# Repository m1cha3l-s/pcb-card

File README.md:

# m1cha3l's PCB Business card V1
You were luck enough to recieve my pcb business card! You can keep it in your wallet and use the built in ruler or solder the needed components and get a nice desk accessories which has a 6x6 NeoPixel MATRIX, 2 buttons, vibration motor for notifications and a BME280 sensor for presure, humidity and temerature and supports Zigbee, Matter, Thread and bluetooth and wifi.

## Building
You can buy the components I have in my bom to build this together! Also I included headers which you can solder to add more sensors for smart home!

## Firmware
I have included a simple firmware which shows red when the temp from BME280 is over 20℃ and green when under when you press button number 2 and vibrates and shows blue when you press button number 1.
1. Open Arduino IDE
2. Choose seeed xiao ESP32-C6
3. Flash and enjoy!!

## Looks

## Schematic and PCB

## [BOM](https://github.com/m1cha3l-s/pcb-card/blob/main/BOM.csv)

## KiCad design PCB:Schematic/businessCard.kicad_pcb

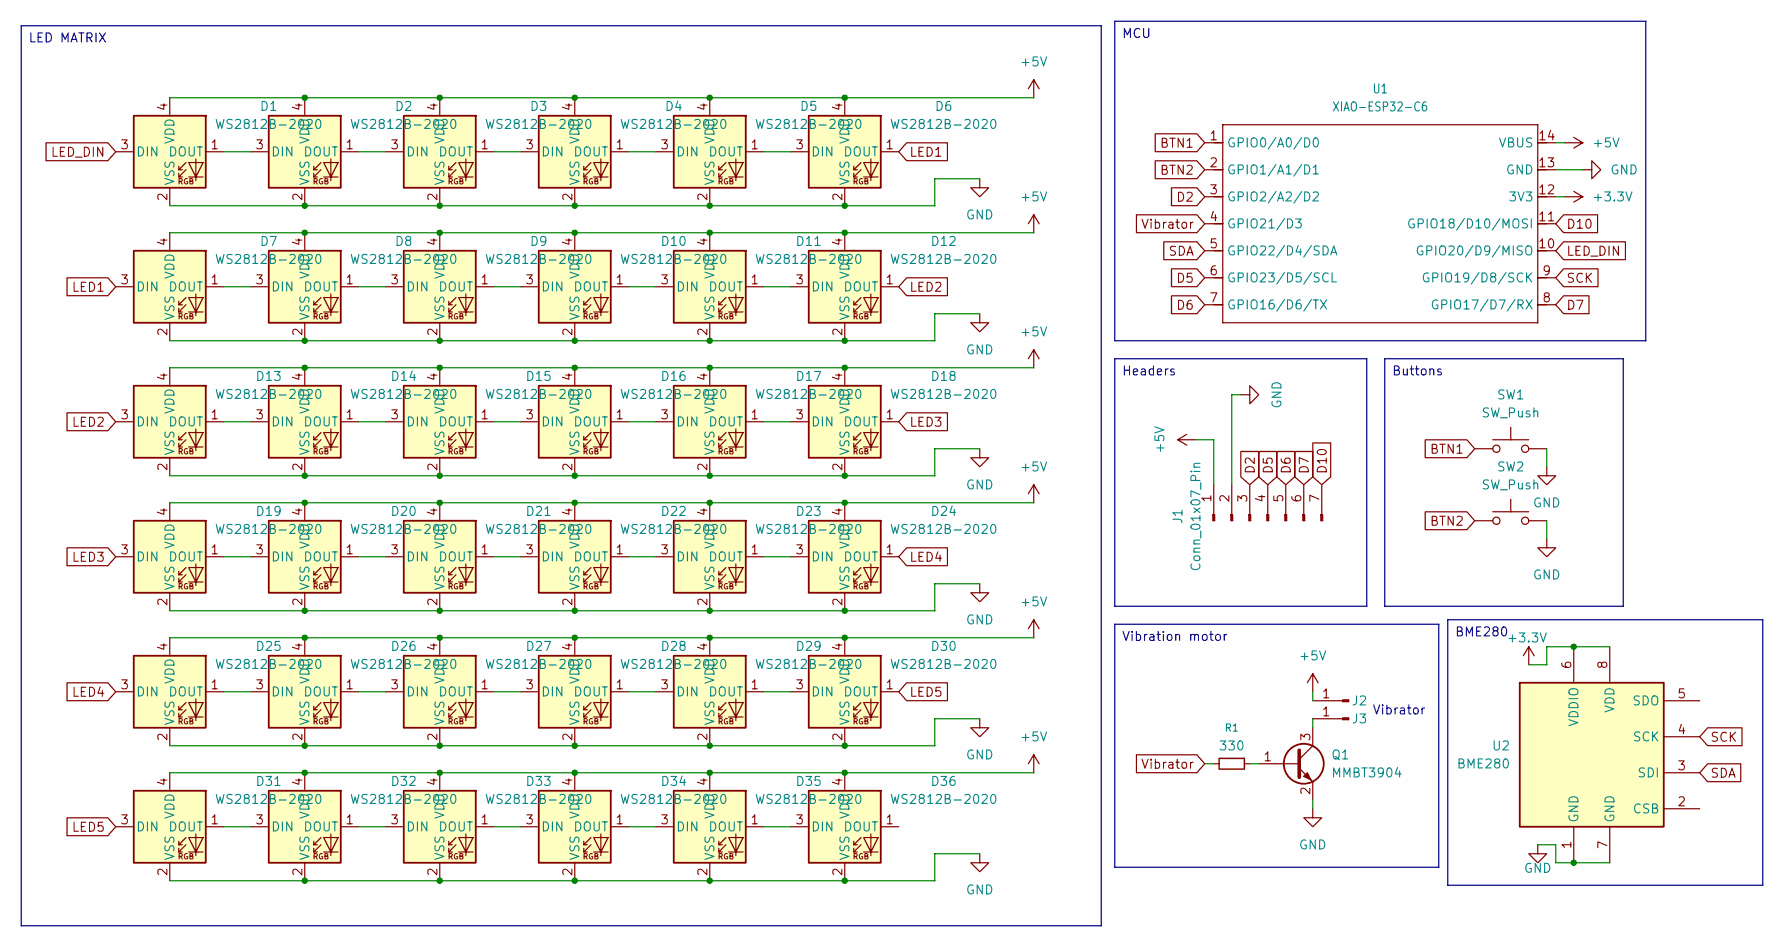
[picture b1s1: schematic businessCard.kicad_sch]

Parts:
D1, D2, D3, D4, D5, D6, D7, D8, D9, D10, D11, D12, D13, D14, D15, D16, D17, D18, D19, D20, D21, D22, D23, D24, D25, D26, D27, D28, D29, D30, D31, D32, D33, D34, D35, D36: WS2812B-2020; LED_WS2812B-2020_PLCC4_2.0x2.0mm
J1: Conn_01x07_Pin; PinHeader_1x07_P2.54mm_Vertical
J2, J3: Conn_01x01_Pin; TestPoint_Pad_2.0x2.0mm
Q1: MMBT3904; SOT-23
R1: 330; R_0603_1608Metric
SW1, SW2: SW_Push; SW_PUSH_6mm_H4.3mm
U1: XIAO-ESP32-C6; XIAO-ESP32C6-DIP
U2: BME280; Bosch_LGA-8_2.5x2.5mm_P0.65mm_ClockwisePinNumbering

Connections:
+3.3V: U1.12 (3V3), U2.6 (VDDIO), U2.8 (VDD)
+5V: D1.4 (VDD), D2.4 (VDD), D3.4 (VDD), D4.4 (VDD), D5.4 (VDD), D6.4 (VDD), D7.4 (VDD), D8.4 (VDD), D9.4 (VDD), D10.4 (VDD), D11.4 (VDD), D12.4 (VDD), D13.4 (VDD), D14.4 (VDD), D15.4 (VDD), D16.4 (VDD), D17.4 (VDD), D18.4 (VDD), D19.4 (VDD), D20.4 (VDD), D21.4 (VDD), D22.4 (VDD), D23.4 (VDD), D24.4 (VDD), D25.4 (VDD), D26.4 (VDD), D27.4 (VDD), D28.4 (VDD), D29.4 (VDD), D30.4 (VDD), D31.4 (VDD), D32.4 (VDD), D33.4 (VDD), D34.4 (VDD), D35.4 (VDD), D36.4 (VDD), J1.1, J2.1, U1.14 (VBUS)
BTN1: SW1.1, U1.1 (GPIO0/A0/D0)
BTN2: SW2.1, U1.2 (GPIO1/A1/D1)
D2: J1.3, U1.3 (GPIO2/A2/D2)
D5: J1.4, U1.6 (GPIO23/D5/SCL)
D6: J1.5, U1.7 (GPIO16/D6/TX)
D7: J1.6, U1.8 (GPIO17/D7/RX)
D10: J1.7, U1.11 (GPIO18/D10/MOSI)
GND: D1.2 (VSS), D2.2 (VSS), D3.2 (VSS), D4.2 (VSS), D5.2 (VSS), D6.2 (VSS), D7.2 (VSS), D8.2 (VSS), D9.2 (VSS), D10.2 (VSS), D11.2 (VSS), D12.2 (VSS), D13.2 (VSS), D14.2 (VSS), D15.2 (VSS), D16.2 (VSS), D17.2 (VSS), D18.2 (VSS), D19.2 (VSS), D20.2 (VSS), D21.2 (VSS), D22.2 (VSS), D23.2 (VSS), D24.2 (VSS), D25.2 (VSS), D26.2 (VSS), D27.2 (VSS), D28.2 (VSS), D29.2 (VSS), D30.2 (VSS), D31.2 (VSS), D32.2 (VSS), D33.2 (VSS), D34.2 (VSS), D35.2 (VSS), D36.2 (VSS), J1.2, Q1.2 (E), SW1.2, SW2.2, U1.13 (GND), U2.1 (GND), U2.7 (GND)
LED1: D6.1 (DOUT), D7.3 (DIN)
LED2: D12.1 (DOUT), D13.3 (DIN)
LED3: D18.1 (DOUT), D19.3 (DIN)
LED4: D24.1 (DOUT), D25.3 (DIN)
LED5: D30.1 (DOUT), D31.3 (DIN)
LED_DIN: D1.3 (DIN), U1.10 (GPIO20/D9/MISO)
unnamed: D1.1 (DOUT), D2.3 (DIN)
unnamed: D2.1 (DOUT), D3.3 (DIN)
unnamed: D3.1 (DOUT), D4.3 (DIN)
unnamed: D4.1 (DOUT), D5.3 (DIN)
unnamed: D5.1 (DOUT), D6.3 (DIN)
unnamed: D7.1 (DOUT), D8.3 (DIN)
unnamed: D8.1 (DOUT), D9.3 (DIN)
unnamed: D9.1 (DOUT), D10.3 (DIN)
unnamed: D10.1 (DOUT), D11.3 (DIN)
unnamed: D11.1 (DOUT), D12.3 (DIN)
unnamed: D13.1 (DOUT), D14.3 (DIN)
unnamed: D14.1 (DOUT), D15.3 (DIN)
unnamed: D15.1 (DOUT), D16.3 (DIN)
unnamed: D16.1 (DOUT), D17.3 (DIN)
unnamed: D17.1 (DOUT), D18.3 (DIN)
unnamed: D19.1 (DOUT), D20.3 (DIN)
unnamed: D20.1 (DOUT), D21.3 (DIN)
unnamed: D21.1 (DOUT), D22.3 (DIN)
unnamed: D22.1 (DOUT), D23.3 (DIN)
unnamed: D23.1 (DOUT), D24.3 (DIN)
unnamed: D25.1 (DOUT), D26.3 (DIN)
unnamed: D26.1 (DOUT), D27.3 (DIN)
unnamed: D27.1 (DOUT), D28.3 (DIN)
unnamed: D28.1 (DOUT), D29.3 (DIN)
unnamed: D29.1 (DOUT), D30.3 (DIN)
unnamed: D31.1 (DOUT), D32.3 (DIN)
unnamed: D32.1 (DOUT), D33.3 (DIN)
unnamed: D33.1 (DOUT), D34.3 (DIN)
unnamed: D34.1 (DOUT), D35.3 (DIN)
unnamed: D35.1 (DOUT), D36.3 (DIN)
unnamed: J3.1, Q1.3 (C)
unnamed: Q1.1 (B), R1.1
SCK: U1.9 (GPIO19/D8/SCK), U2.4 (SCK)
SDA: U1.5 (GPIO22/D4/SDA), U2.3 (SDI)
Vibrator: R1.2, U1.4 (GPIO21/D3)

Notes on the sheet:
Vibrator
Headers
LED MATRIX
MCU
BME280
Buttons
Vibration motor

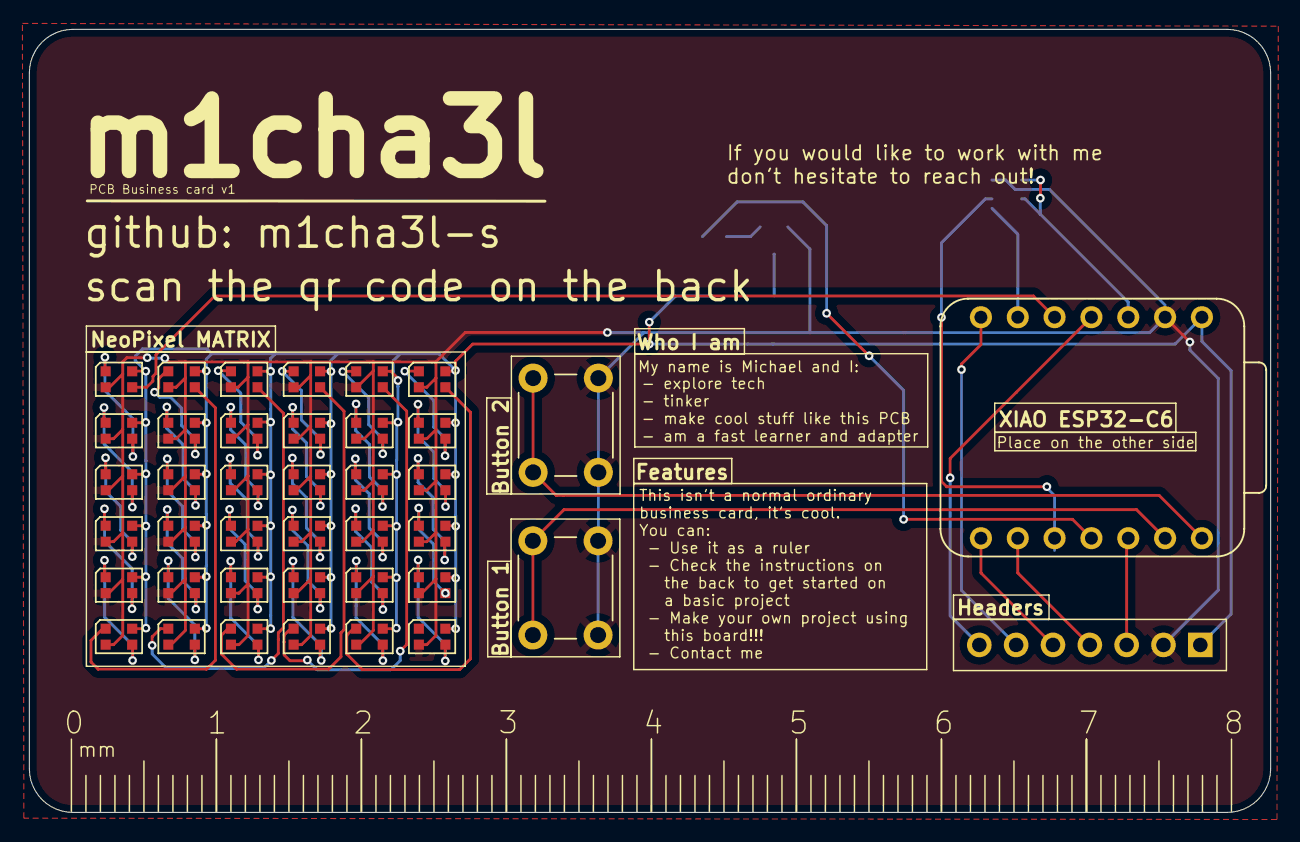
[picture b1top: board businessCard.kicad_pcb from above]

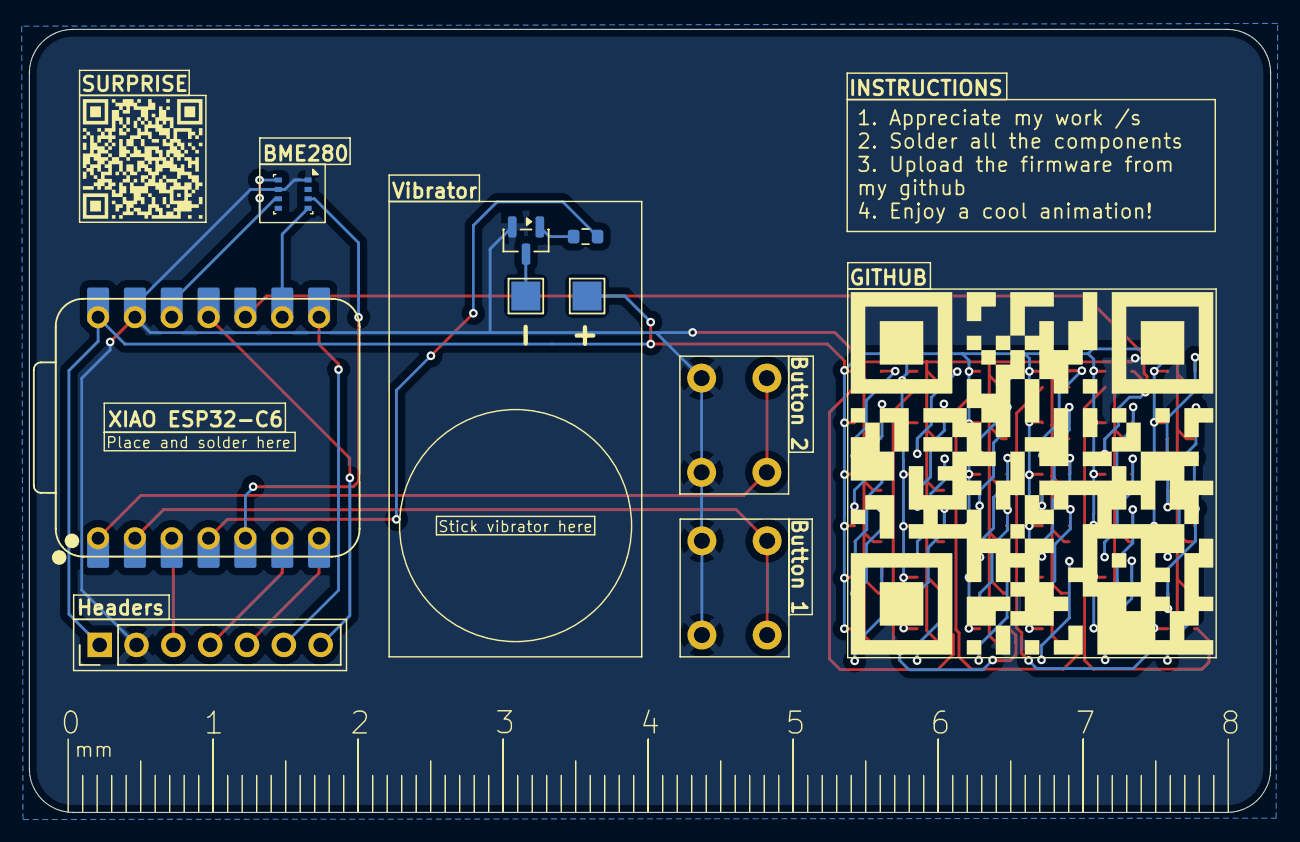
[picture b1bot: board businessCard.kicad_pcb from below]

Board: 2 copper layers, 85.6 x 54.0 mm, 47 parts (9 on the bottom side), 51 nets.

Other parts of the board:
QR*****: https://www.youtube.com/watch?v=dQw4w9WgXcQ; //www.youtube.com/watch?v=dQw4w9WgXcQ
QR*****#2: big-githubqr

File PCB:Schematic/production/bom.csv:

Designator,Footprint,Quantity,Value,LCSC Part #
,f06da421-139f-4461-bd72-0d63481e1e29,1,,
"D1, D10, D11, D12, D13, D14, D15, D16, D17, D18, D19, D2, D20, D21, D22, D23, D24, D25, D26, D27, D28, D29, D3, D30, D31, D32, D33, D34, D35, D36, D4, D5, D6, D7, D8, D9",LED_WS2812B-2020_PLCC4_2.0x2.0mm,36,WS2812B-2020,
J1,PinHeader_1x07_P2.54mm_Vertical,1,Conn_01x07_Pin,
"J2, J3",TestPoint_Pad_2.0x2.0mm,2,Conn_01x01_Pin,
Q1,SOT-23,1,MMBT3904,
R1,0603,1,330,
"SW1, SW2",SW_PUSH_6mm_H4.3mm,2,SW_Push,
U1,XIAO-ESP32C6-DIP,1,XIAO-ESP32-C6,
U2,Bosch_LGA-8_2.5x2.5mm_P0.65mm_ClockwisePinNumbering,1,BME280,

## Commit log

2026-03-30 Added pcb source and gerbers + BOM
2026-03-30 added pics
2026-04-16 Read BME280 temp and animate it on LED matrix
    Agent-Logs-Url: https://github.com/m1cha3l-s/pcb-card/sessions/6416371f-6edf-4c9a-95ea-39f87f6afe48
2026-04-16 Handle BME280 init failure safely
    Agent-Logs-Url: https://github.com/m1cha3l-s/pcb-card/sessions/6416371f-6edf-4c9a-95ea-39f87f6afe48
2026-04-16 Make temperature animation non-blocking
    Agent-Logs-Url: https://github.com/m1cha3l-s/pcb-card/sessions/6416371f-6edf-4c9a-95ea-39f87f6afe48
2026-04-16 Clean up temp text buffer and duplicate color setup
    Agent-Logs-Url: https://github.com/m1cha3l-s/pcb-card/sessions/6416371f-6edf-4c9a-95ea-39f87f6afe48
2026-04-16 Add debounce and rollover-safe temp animation timing
    Agent-Logs-Url: https://github.com/m1cha3l-s/pcb-card/sessions/6416371f-6edf-4c9a-95ea-39f87f6afe48
2026-04-16 Simplify button 2 to direct BME280 temp display
    Agent-Logs-Url: https://github.com/m1cha3l-s/pcb-card/sessions/3cddab59-1e9f-45e8-9866-2d50be3431a8
2026-04-16 changed button2 to fill matrix based on temp
2026-04-16 button1 now shows blue on the matrix
2026-04-16 added updated pcb stuff
2026-04-16 new pcb pic
2026-04-16 Added serial print functions
